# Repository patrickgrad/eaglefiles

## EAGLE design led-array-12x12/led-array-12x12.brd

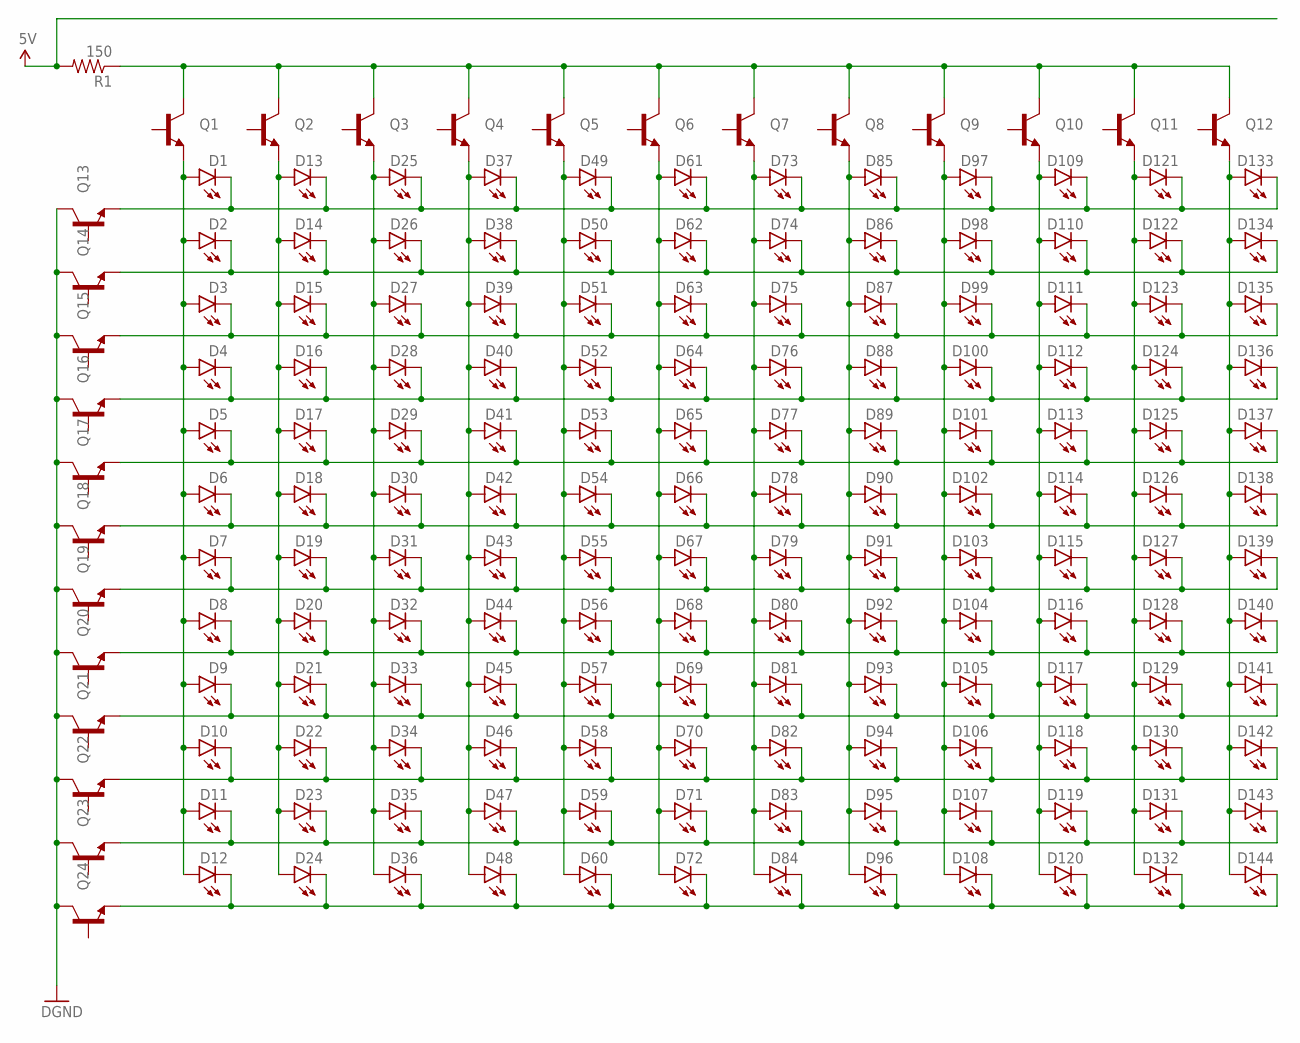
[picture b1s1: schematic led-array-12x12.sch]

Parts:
D1, D2, D3, D4, D5, D6, D7, D8, D9, D10, D11, D12, D13, D14, D15, D16, D17, D18, D19, D20, D21, D22, D23, D24, D25, D26, D27, D28, D29, D30, D31, D32, D33, D34, D35, D36, D37, D38, D39, D40, D41, D42, D43, D44, D45, D46, D47, D48, D49, D50, D51, D52, D53, D54, D55, D56, D57, D58, D59, D60, D61, D62, D63, D64, D65, D66, D67, D68, D69, D70, D71, D72, D73, D74, D75, D76, D77, D78, D79, D80, D81, D82, D83, D84, D85, D86, D87, D88, D89, D90, D91, D92, D93, D94, D95, D96, D97, D98, D99, D100, D101, D102, D103, D104, D105, D106, D107, D108, D109, D110, D111, D112, D113, D114, D115, D116, D117, D118, D119, D120, D121, D122, D123, D124, D125, D126, D127, D128, D129, D130, D131, D132, D133, D134, D135, D136, D137, D138, D139, D140, D141, D142, D143, D144: LED-IR-THRUTSAL6100; LED5MM
Q1, Q2, Q3, Q4, Q5, Q6, Q7, Q8, Q9, Q10, Q11, Q12, Q13, Q14, Q15, Q16, Q17, Q18, Q19, Q20, Q21, Q22, Q23, Q24: TRANSISTOR_NPNMMBT2222A; SOT23-3
R1: 150; 0805

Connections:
5V: R1.2
GND: Q13.3 (C), Q14.3 (C), Q15.3 (C), Q16.3 (C), Q17.3 (C), Q18.3 (C), Q19.3 (C), Q20.3 (C), Q21.3 (C), Q22.3 (C), Q23.3 (C), Q24.3 (C)
unnamed: D1.A, D2.A, D3.A, D4.A, D5.A, D6.A, D7.A, D8.A, D9.A, D10.A, D11.A, D12.A, Q1.2 (E)
unnamed: D13.A, D14.A, D15.A, D16.A, D17.A, D18.A, D19.A, D20.A, D21.A, D22.A, D23.A, D24.A, Q2.2 (E)
unnamed: D25.A, D26.A, D27.A, D28.A, D29.A, D30.A, D31.A, D32.A, D33.A, D34.A, D35.A, D36.A, Q3.2 (E)
unnamed: D37.A, D38.A, D39.A, D40.A, D41.A, D42.A, D43.A, D44.A, D45.A, D46.A, D47.A, D48.A, Q4.2 (E)
unnamed: D49.A, D50.A, D51.A, D52.A, D53.A, D54.A, D55.A, D56.A, D57.A, D58.A, D59.A, D60.A, Q5.2 (E)
unnamed: D61.A, D62.A, D63.A, D64.A, D65.A, D66.A, D67.A, D68.A, D69.A, D70.A, D71.A, D72.A, Q6.2 (E)
unnamed: D73.A, D74.A, D75.A, D76.A, D77.A, D78.A, D79.A, D80.A, D81.A, D82.A, D83.A, D84.A, Q7.2 (E)
unnamed: D85.A, D86.A, D87.A, D88.A, D89.A, D90.A, D91.A, D92.A, D93.A, D94.A, D95.A, D96.A, Q8.2 (E)
unnamed: D97.A, D98.A, D99.A, D100.A, D101.A, D102.A, D103.A, D104.A, D105.A, D106.A, D107.A, D108.A, Q9.2 (E)
unnamed: D109.A, D110.A, D111.A, D112.A, D113.A, D114.A, D115.A, D116.A, D117.A, D118.A, D119.A, D120.A, Q10.2 (E)
unnamed: D121.A, D122.A, D123.A, D124.A, D125.A, D126.A, D127.A, D128.A, D129.A, D130.A, D131.A, D132.A, Q11.2 (E)
unnamed: D133.A, D134.A, D135.A, D136.A, D137.A, D138.A, D139.A, D140.A, D141.A, D142.A, D143.A, D144.A, Q12.2 (E)
unnamed: D1.K (C), D13.K (C), D25.K (C), D37.K (C), D49.K (C), D61.K (C), D73.K (C), D85.K (C), D97.K (C), D109.K (C), D121.K (C), D133.K (C), Q13.2 (E)
unnamed: D2.K (C), D14.K (C), D26.K (C), D38.K (C), D50.K (C), D62.K (C), D74.K (C), D86.K (C), D98.K (C), D110.K (C), D122.K (C), D134.K (C), Q14.2 (E)
unnamed: D8.K (C), D20.K (C), D32.K (C), D44.K (C), D56.K (C), D68.K (C), D80.K (C), D92.K (C), D104.K (C), D116.K (C), D128.K (C), D140.K (C), Q20.2 (E)
unnamed: D3.K (C), D15.K (C), D27.K (C), D39.K (C), D51.K (C), D63.K (C), D75.K (C), D87.K (C), D99.K (C), D111.K (C), D123.K (C), D135.K (C), Q15.2 (E)
unnamed: Q1.3 (C), Q2.3 (C), Q3.3 (C), Q4.3 (C), Q5.3 (C), Q6.3 (C), Q7.3 (C), Q8.3 (C), Q9.3 (C), Q10.3 (C), Q11.3 (C), Q12.3 (C), R1.1
unnamed: D4.K (C), D16.K (C), D28.K (C), D40.K (C), D52.K (C), D64.K (C), D76.K (C), D88.K (C), D100.K (C), D112.K (C), D124.K (C), D136.K (C), Q16.2 (E)
unnamed: D5.K (C), D17.K (C), D29.K (C), D41.K (C), D53.K (C), D65.K (C), D77.K (C), D89.K (C), D101.K (C), D113.K (C), D125.K (C), D137.K (C), Q17.2 (E)
unnamed: D6.K (C), D18.K (C), D30.K (C), D42.K (C), D54.K (C), D66.K (C), D78.K (C), D90.K (C), D102.K (C), D114.K (C), D126.K (C), D138.K (C), Q18.2 (E)
unnamed: D7.K (C), D19.K (C), D31.K (C), D43.K (C), D55.K (C), D67.K (C), D79.K (C), D91.K (C), D103.K (C), D115.K (C), D127.K (C), D139.K (C), Q19.2 (E)
unnamed: D9.K (C), D21.K (C), D33.K (C), D45.K (C), D57.K (C), D69.K (C), D81.K (C), D93.K (C), D105.K (C), D117.K (C), D129.K (C), D141.K (C), Q21.2 (E)
unnamed: D10.K (C), D22.K (C), D34.K (C), D46.K (C), D58.K (C), D70.K (C), D82.K (C), D94.K (C), D106.K (C), D118.K (C), D130.K (C), D142.K (C), Q22.2 (E)
unnamed: D11.K (C), D23.K (C), D35.K (C), D47.K (C), D59.K (C), D71.K (C), D83.K (C), D95.K (C), D107.K (C), D119.K (C), D131.K (C), D143.K (C), Q23.2 (E)
unnamed: D12.K (C), D24.K (C), D36.K (C), D48.K (C), D60.K (C), D72.K (C), D84.K (C), D96.K (C), D108.K (C), D120.K (C), D132.K (C), D144.K (C), Q24.2 (E)

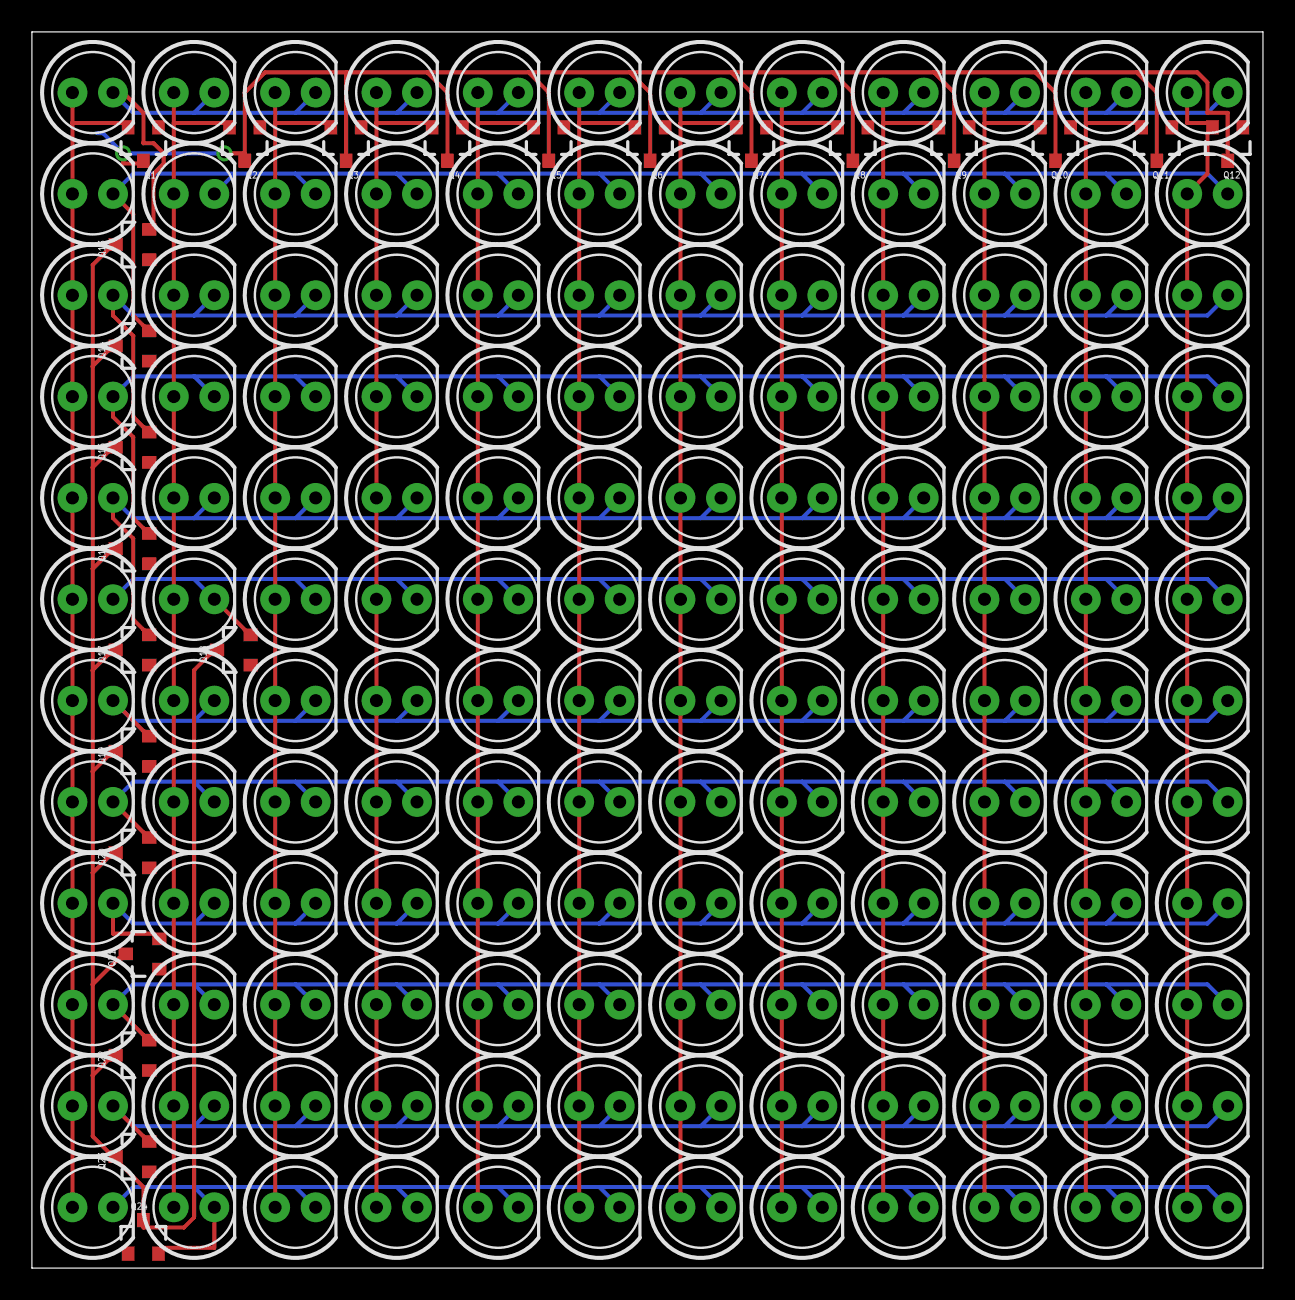
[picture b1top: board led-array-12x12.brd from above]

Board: 2 copper layers, 77.1 x 77.5 mm, 169 parts (0 on the bottom side), 26 nets.

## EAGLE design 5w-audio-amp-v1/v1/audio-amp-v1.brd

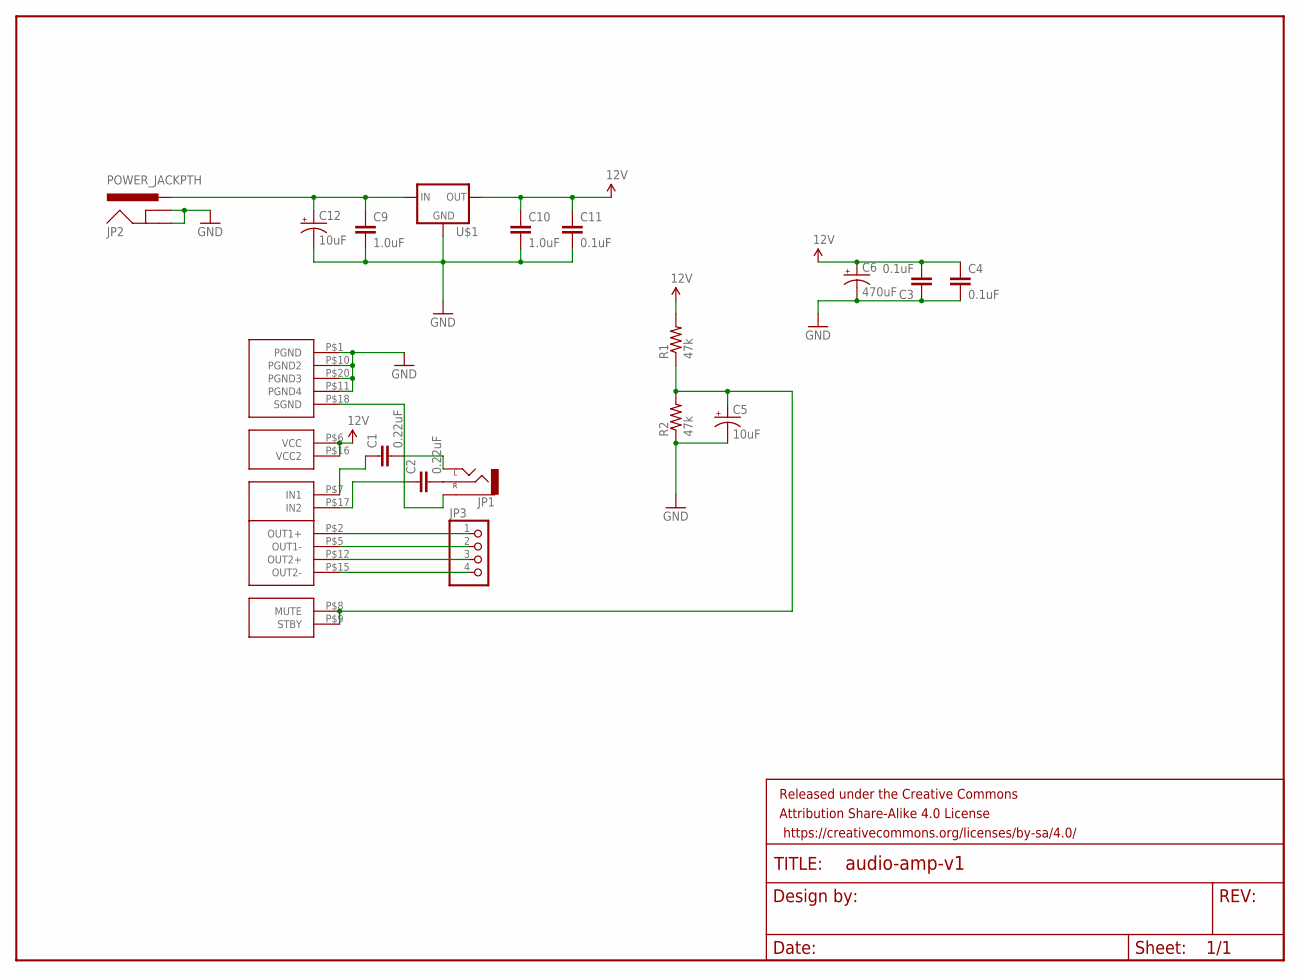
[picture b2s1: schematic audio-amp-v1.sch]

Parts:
C1, C2: 0.22uF; 0603-CAP
C3, C4, C11: 0.1uF; 0603-CAP
C5, C12: 10uF; PANASONIC_C
C6: 470uF; NIC_10X10.5_CAP
C9, C10: 1.0uF; 0603-CAP
FRAME1: FRAME-LETTERNO_PACKAGE; DUMMY
JP1: AUDIO-JACKSMD2; AUDIO-JACK-3.5MM-SMD
JP2: POWER_JACKPTH; POWER_JACK_PTH
JP3: PINHD-1X4; 1X04
R1, R2: 47k; 0603-RES
U$1: V_REG_78XX-TO-220; TO-220-ALT
U$2: TDA7266D

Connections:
5V: C3.2, C4.1, C6.+, C10.1, C11.1, R1.2, U$1.OUT, U$2.P$6 (VCC), U$2.P$16 (VCC2)
GND: C3.1, C4.2, C5.-, C6.-, C9.2, C10.2, C11.2, C12.-, JP2.GND, JP2.GNDBREAK, R2.1, U$1.GND, U$2.P$1 (PGND), U$2.P$10 (PGND2), U$2.P$11 (PGND4), U$2.P$20 (PGND3)
unnamed: C2.1, U$2.P$17 (IN2)
unnamed: C1.1, U$2.P$7 (IN1)
unnamed: JP3.1, U$2.P$2 (OUT1+)
unnamed: JP3.2, U$2.P$5 (OUT1-)
unnamed: JP3.3, U$2.P$12 (OUT2+)
unnamed: JP3.4, U$2.P$15 (OUT2-)
unnamed: JP1.SLEEVE, U$2.P$18 (SGND)
unnamed: C2.2, JP1.RING (RIGHT)
unnamed: C1.2, JP1.TIP (LEFT)
unnamed: C5.+, R1.1, R2.2, U$2.P$8 (MUTE), U$2.P$9 (STBY)
unnamed: C9.1, C12.+, JP2.PWR, U$1.IN

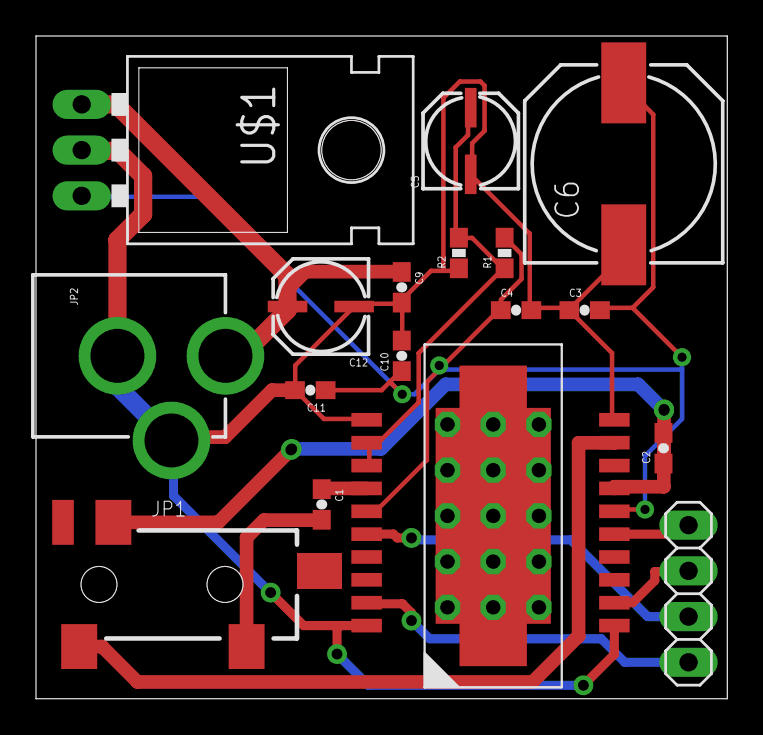
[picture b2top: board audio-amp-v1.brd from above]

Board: 2 copper layers, 38.4 x 36.8 mm, 18 parts (0 on the bottom side), 13 nets.

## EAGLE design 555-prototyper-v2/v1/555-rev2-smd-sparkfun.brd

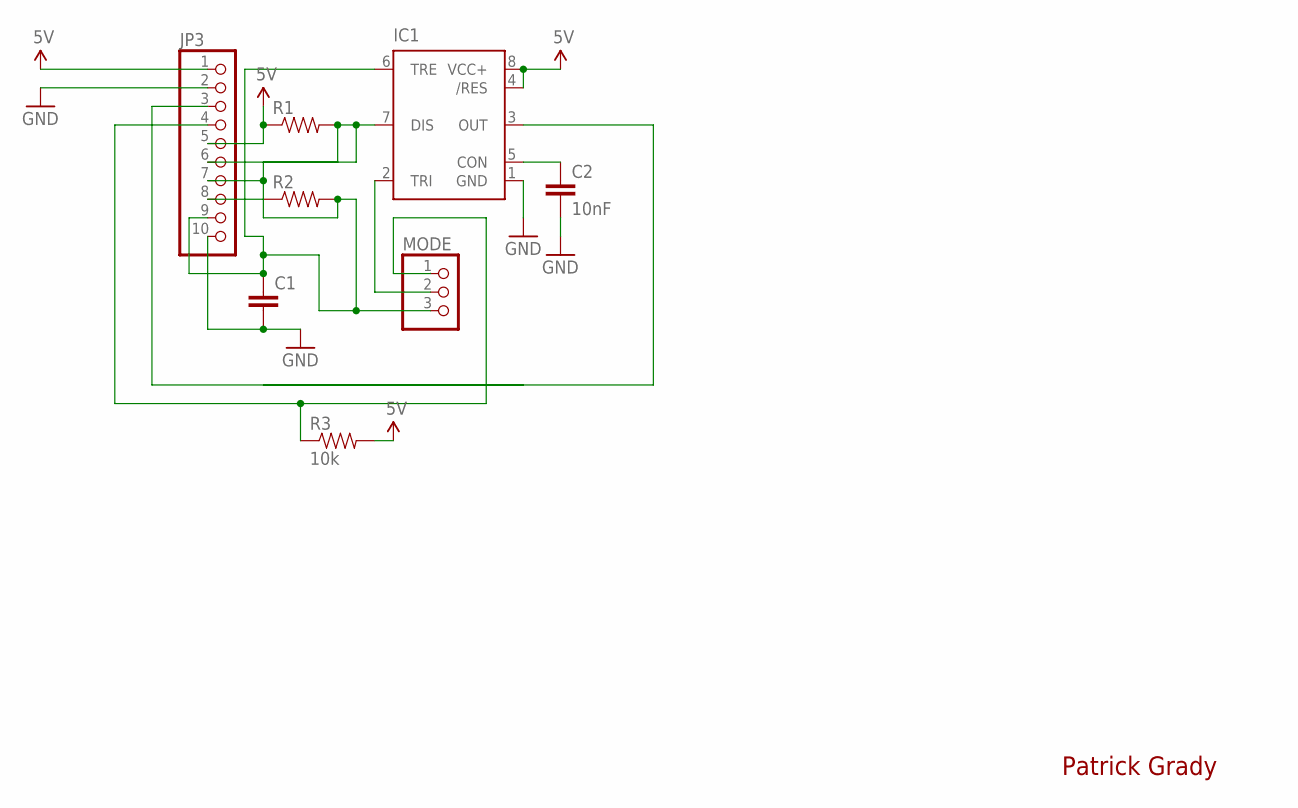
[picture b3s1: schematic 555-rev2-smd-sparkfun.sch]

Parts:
C1: CAPEZ; CAP-PTH-SMALLEZ
C2: 10nF; 0603-CAP
IC1: NE555D; SO08
JP3: PINHD-1X10; 1X10
MODE: PINHD-1X3; 1X03
R1, R2: RESISTOREZ; AXIAL-0.3EZ
R3: 10k; 0603-RES

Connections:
5V: IC1.4 (/RES), IC1.8 (VCC+), JP3.1, JP3.5, R1.P$1 (1), R3.2
GND: C1.2, C2.2, IC1.1 (GND), JP3.2, JP3.10
unnamed: IC1.7 (DIS), JP3.6, JP3.7, R1.P$2 (2), R2.P$1 (1)
unnamed: JP3.4, MODE.1, R3.1
unnamed: C2.1, IC1.5 (CON)
unnamed: C1.1, IC1.6 (TRE), JP3.8, JP3.9, MODE.3, R2.P$2 (2)
unnamed: IC1.3 (OUT), JP3.3
unnamed: IC1.2 (TRI), MODE.2

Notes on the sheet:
Patrick Grady

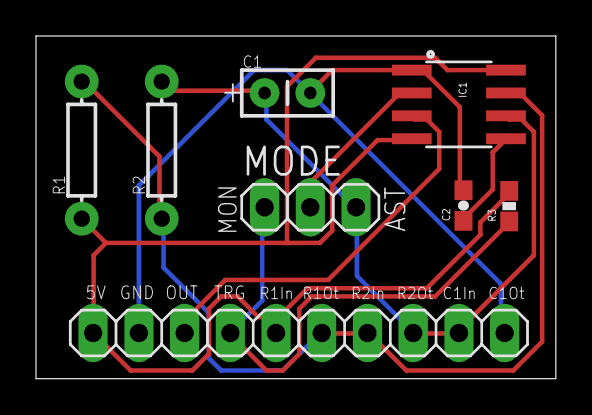
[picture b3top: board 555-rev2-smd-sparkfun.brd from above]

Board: 2 copper layers, 28.9 x 19.0 mm, 8 parts (0 on the bottom side), 8 nets.

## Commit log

2015-10-12 EAGLE files
    EAGLE CAD files for a few different projects.
2016-01-26 Get rid of svn files
2019-07-30 done with v3 and new cam files

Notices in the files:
parts and their libraries:
SparkFun-AnalogIC: Licensing:Creative Commons ShareAlike 4.0 International - https://creativecommons.org/licenses/by-sa/4.0
SparkFun-Aesthetics: Released under the Creative Commons Attribution Share-Alike 4.0 License
SparkFun-Aesthetics: https://creativecommons.org/licenses/by-sa/4.0
